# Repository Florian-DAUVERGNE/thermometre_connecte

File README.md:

# thermometre_connecte
thermomètre connecté codé avec Arduino

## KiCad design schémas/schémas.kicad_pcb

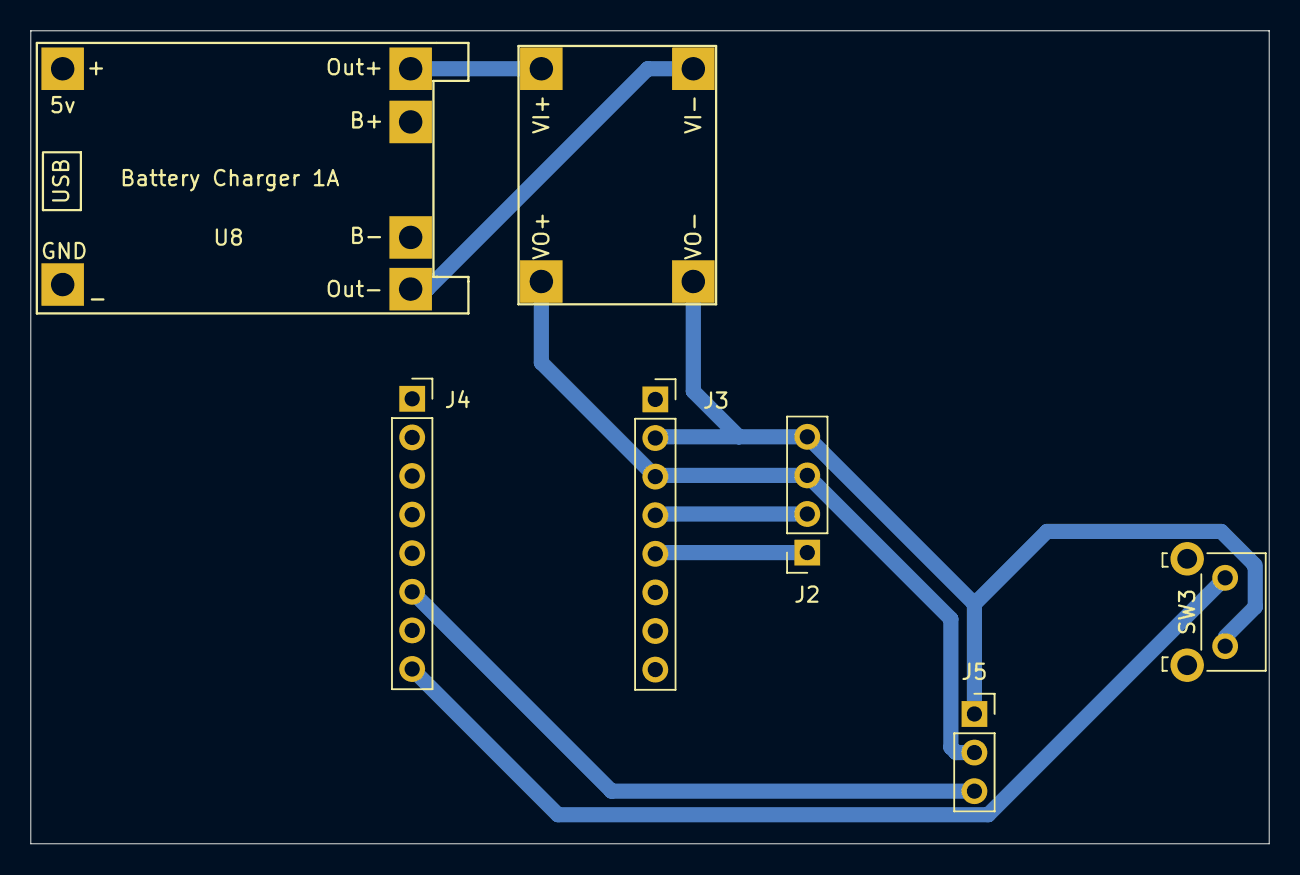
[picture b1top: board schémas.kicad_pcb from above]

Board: 2 copper layers, 81.5 x 53.5 mm, 7 parts (0 on the bottom side), 8 nets.

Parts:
J2: Conn_01x04; PinSocket_1x04_P2.54mm_Vertical
J3, J4: Conn_01x08; PinSocket_1x08_P2.54mm_Vertical
J5: Conn_01x03; PinSocket_1x03_P2.54mm_Vertical
SW3: SW_Push; SW_Tactile_SKHH_Angled
U8: TP4056-18650
U9: Voltage_Regulator_3.3V

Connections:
+3.3V: J2.3, J3.3, J5.2, U9.4 (VO+)
GND: J2.4, J3.2, J5.1, SW3.2, U9.3 (VO-)
unnamed: J2.1, J3.5
unnamed: J2.2, J3.4
unnamed: J4.6, J5.3
unnamed: J4.8, SW3.1
unnamed: U8.3 (OUT+), U9.2 (VI+)
unnamed: U8.4 (OUT-), U9.1 (VI-)

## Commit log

2026-01-04 feat: test code
2026-01-04 refactor: changed name
2026-01-04 refactor: made a class
2026-01-04 refactor: made a receiver class
2026-01-04 refactor: created a DHT class
2026-01-04 refactor: changed name to CapteurDHT
2026-01-04 feat: made a 7 segments class
2026-01-04 refactor moved classes to lib
2026-01-04 refactor: changed link
2026-01-04 refactor: moved message stuct
2026-01-04 feat: main code
2026-01-05 refactor: removed negative temp
2026-01-05 refactor: better lighting handling
2026-01-05 feat: added display clear function
2026-01-05 feat: added function to display humidity
2026-01-05 feat: added display error function
2026-01-05 feat: added brightness function
2026-01-05 style: formated afficheur7segments.h
2026-01-05 feat: added led blinkink on receive
2026-01-05 feat: added humidity to message
2026-01-05 feat: included all new features
2026-01-06 style: formated espnow_receiver.h
2026-01-06 feat: message can now be acceced
2026-01-06 refactor: moved code to functions
2026-01-06 feat: made code for connected relay
2026-01-08 feat: display shut off after 1m
2026-01-08 refactor: changed initial state
2026-01-18 feat: added .gitignore
2026-01-18 refactor: changed pin
2026-01-18 feat: added kicad schema
2026-01-18 feat: added button to diagram
2026-01-18 refactor: changed button pin
2026-01-30 feat: changed schemas
2026-03-11 feat: added new features
2026-03-11 feat: created SHT41 lib
2026-03-11 feat: changed DHT to SHT
2026-03-11 refactor: inverted temperatures
